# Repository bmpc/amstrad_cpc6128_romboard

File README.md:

# Amstrad CPC 6128 ROM Board

A ROM Board for the Amstrad CPC 6128 capable of loading two expansion ROMs simultaneously from an SD card.

Nowadays, there are plenty of [ROMS available for the Amstrad CPC](http://www.cpcwiki.eu/index.php/ROM_List).
This board allows you to load any ROM present on an SD card as an expansion ROM on the Amstrad CPC 6128. You can bank up to two ROMs at the same time since there are many programs and games that require two ROMs loaded concurrently. In order to select which expansion ROMs should be made available for the Amstrad CPC, the ROM Board provides a small OLED display and buttons that allow the user to browse the SD card files and choose the Upper and Lower ROM specifically.

The ROM board connects to the [expansion port](https://www.cpcwiki.eu/index.php/Connector:Expansion_port) of the Amstrad CPC6128. Here is a picture of the assembled board:

<div style="margin-bottom:20px;">
  
</div>

&nbsp;

## User interface

Upon startup, the selected ROMs for the upper and lower positions are loaded to the SRAM. The display shows the loading progress of each ROM. Once the ROMS are loaded, the display shows the ROM names that are currently loaded.

In order to select ROMs from the SD card, five buttons are provided so that the user can:
 - **SELECT** a given ROM for the upper or lower ROM position
 - **CANCEL** the selected action and return to the loaded ROMs initial screen.
 - Move **UP** and **DOWN** the ROM root folder on the SD card
 - **RESET** the Amstrad CPC and the ROM Board

**Browsing ROMs:**

 - From the main screen, click on the UP or DOWN buttons to enter the browsing mode.
 - In browsing mode, navigate using the UP and DOWN buttons to choose a ROM file from the SD card.

**Selecting a ROM:**

 - Once the desired ROM is chosen, press the SELECT button.
 - A new screen will appear, prompting the user to select the ROM bank position: Lower or Upper.
 - Switch between the lower and upper bank by using the UP and DOWN buttons.

**Saving the ROM:**

 - Press the SELECT button to save the ROM file on the selected bank.
 - To complete the process, restart the Amstrad CPC. This can be done by turning off and on the computer or using the RESET button on the ROM Board.

**Canceling ROM Selection:**

 - If you wish to cancel the ROM selection, press the CANCEL button.
 - You will be returned to the main screen.

## Demonstration video

## The circuit

The circuit can be divided into two parts:
 1. ROM loading, browsing and selection
 2. ROM expansion interface with the Amstrad CPC

The common part between them is the address bugs, the data bus and the SRAM that holds the loaded ROMs.

Ensuring that only one device assumes control of the bus at all times is a crucial aspect to consider. Because we are using the same address and data bus of the Amstrad CPC, when the Amstrad CPC is accessing the bus, the ROM Board shift registers must be tri-stated. Likewise, whenever the ROM Board is accessing the bus in order to load the ROMs, the Amstrad CPC must release control of the bus. This is accomplished by requesting control of the bus through the BUSREQ line being pulled low.

### ROM loading, browsing and selection

The ROM board is based on a atmega328p microcontroller, the same microcontroller that you can find on development boards such as the Arduino Uno. The atmega328p is responsible for loading the selected ROMs (upper and lower) from the SD card into a 32K SRAM (**AS6C62256A**) when the Amstrad CPC boots up.

The loading duration for both ROMs is approximately 5 seconds. Therefore, we need a way to hold the CPC6128 until the ROMs finish loading. This can be achieved using the **BUSREQ** and **BUSACK** lines on the Z80. When the Amstrad CPC starts up, the ROM Board will immediately pull the **BUSREQ** LOW with a pull low resistor. Once the **BUSACK** line is LOW, the Z80 is signaling that control of the address bus, data bus and output signals has been released, and our ROM Board can take control and it starts loading the ROMs. When the atmega328p finishes loading the ROMS, it will pull the **BUSREQ** HIGH and the Z80 resumes processing.

In order to copy the ROM data from the SD card into the SRAM memory, three 8-bit shift registers are used as there aren't enough GPIO pins on the atmega328p for the 15 address lines, 8 data lines and multiple other control signals needed for the ROM board.

Once the ROMs are loaded and the Amstrad CPC has completed the boot process, the user can interact with the ROM Board in order to configure additional ROMs by browsing the SD card and selecting the Upper and Lower ROM. The selected ROMs will be saved within the atmega328p internal EEPROM. In order to load the newly selected ROMs, the Amstrad CPC and the ROM Board must be restarted.

### ROM expansion interface with the Amstrad CPC

Whenever the CPC wants to communicate with the Upper ROM, it will first write a byte with the selected Upper ROM bank number into port **$DF00**. There can be up to 252 expansion ROMS mapped over the top 16K of memory, starting at #C000. After this, the **ROMEN** signal will go LOW, and the CPC will start addressing the Upper ROM.

We must guarantee that there is a unique Upper ROM enabled at any given time. Therefore, whenever an expansion ROM is active, the internal CPC Upper ROM must be disabled. This is done by bringing the **ROMDIS** line LOW, a signal conveniently provided by the CPC for this purpose. After this, any memory requests to the ROM’s address space will be handled solely by the selected expansion ROM.

The CPC does not store the selected ROM Bank number anywhere. Peripheral devices are responsible for latching the selected ROM bank whenever the bank number is written to port **$DF00**.

Our ROM Board supports up to two ROMs mapped for the Amstrad CPC Upper ROM bank. These ROMs are located at positions **#14** and **#15** (that we call Upper and Lower ROMS on the ROM Board).

Whenever the Amstrad CPC tries to select a given ROM through the IO port, if the ROM being selected is provided by the ROM Board (#14 or #15) then a latch is used to store this information. Another latch is used to store which of the ROMs was selected: #14 or #15. A Dual D-Type flipflop (SN74HC74N) was used for these latches.

The Tristate buffer (SN74HC126N) is used to tie the A14 line to the selected upper or lower ROM stored in the previous latch. The A14 line must be tri-stated from the Amstrad CPC bus whenever the ROMS are being loaded.

You can find more detail information regarding the build of this ROM Board in the following post:
[https://bmpc.github.io/amstrad-cpc-rom-board](https://bmpc.github.io/amstrad-cpc-rom-board/).

### Schematic

<div style="text-align:center">
  
</div>

### BOM

 - Atmega328             x1
 - 74HC595N              x3 (shift registers)
 - 74HC74N               x1 (D FlipFlop)
 - 74HC21N               x2 (Dual 4-input AND gate)
 - 74HC126N              x1 (3-state bus buffer)
 - 74HC02N               x1 (Quad 2-input NOR gate)
 - AS6C62256A            x1 (32k sram)
 - 10kΩ  resistor        x1
 - 1.8Ω  resistor        x1
 - 1Ω    resistor        x5
 - 220Ω  resistor        x1
 - 1N4148                x1 (Standard Diode 300mA 75V)
 - 22pF 50V capacitor    x2
 - Push Buttons          x5
 - Cristal 16Mhz         x1
 - MicroSD card breakout x1 (adafruit)
 - 0.96inch OLED         x1 (0.96inch OLED 128X64 w/ SPI/I2C interfaces and vertical pinheader 4pin - White)
 - 02x25 socket          x1 (expansion port)

## References

 - [Building an Amstrad CPC expansion ROM in a breadboard](https://bmpc.github.io/bulding-an-amstrad-cpc-expansion-rom)
 - [Amstrad CPC 6128 ROM Board](https://bmpc.github.io/amstrad-cpc-rom-board)
 - https://www.cpcwiki.eu/index.php/ACU_Romboard_(DIY)
 - https://www.cpcwiki.eu/imgs/3/32/Amstrad_rom_expander.pdf

## *Disclaimer*
*I'm a software engineer with no background in electronics. Please don't consider what you read here to be best practice. Use at your own risk.*

*Nevertheless, feedback is always welcome.*

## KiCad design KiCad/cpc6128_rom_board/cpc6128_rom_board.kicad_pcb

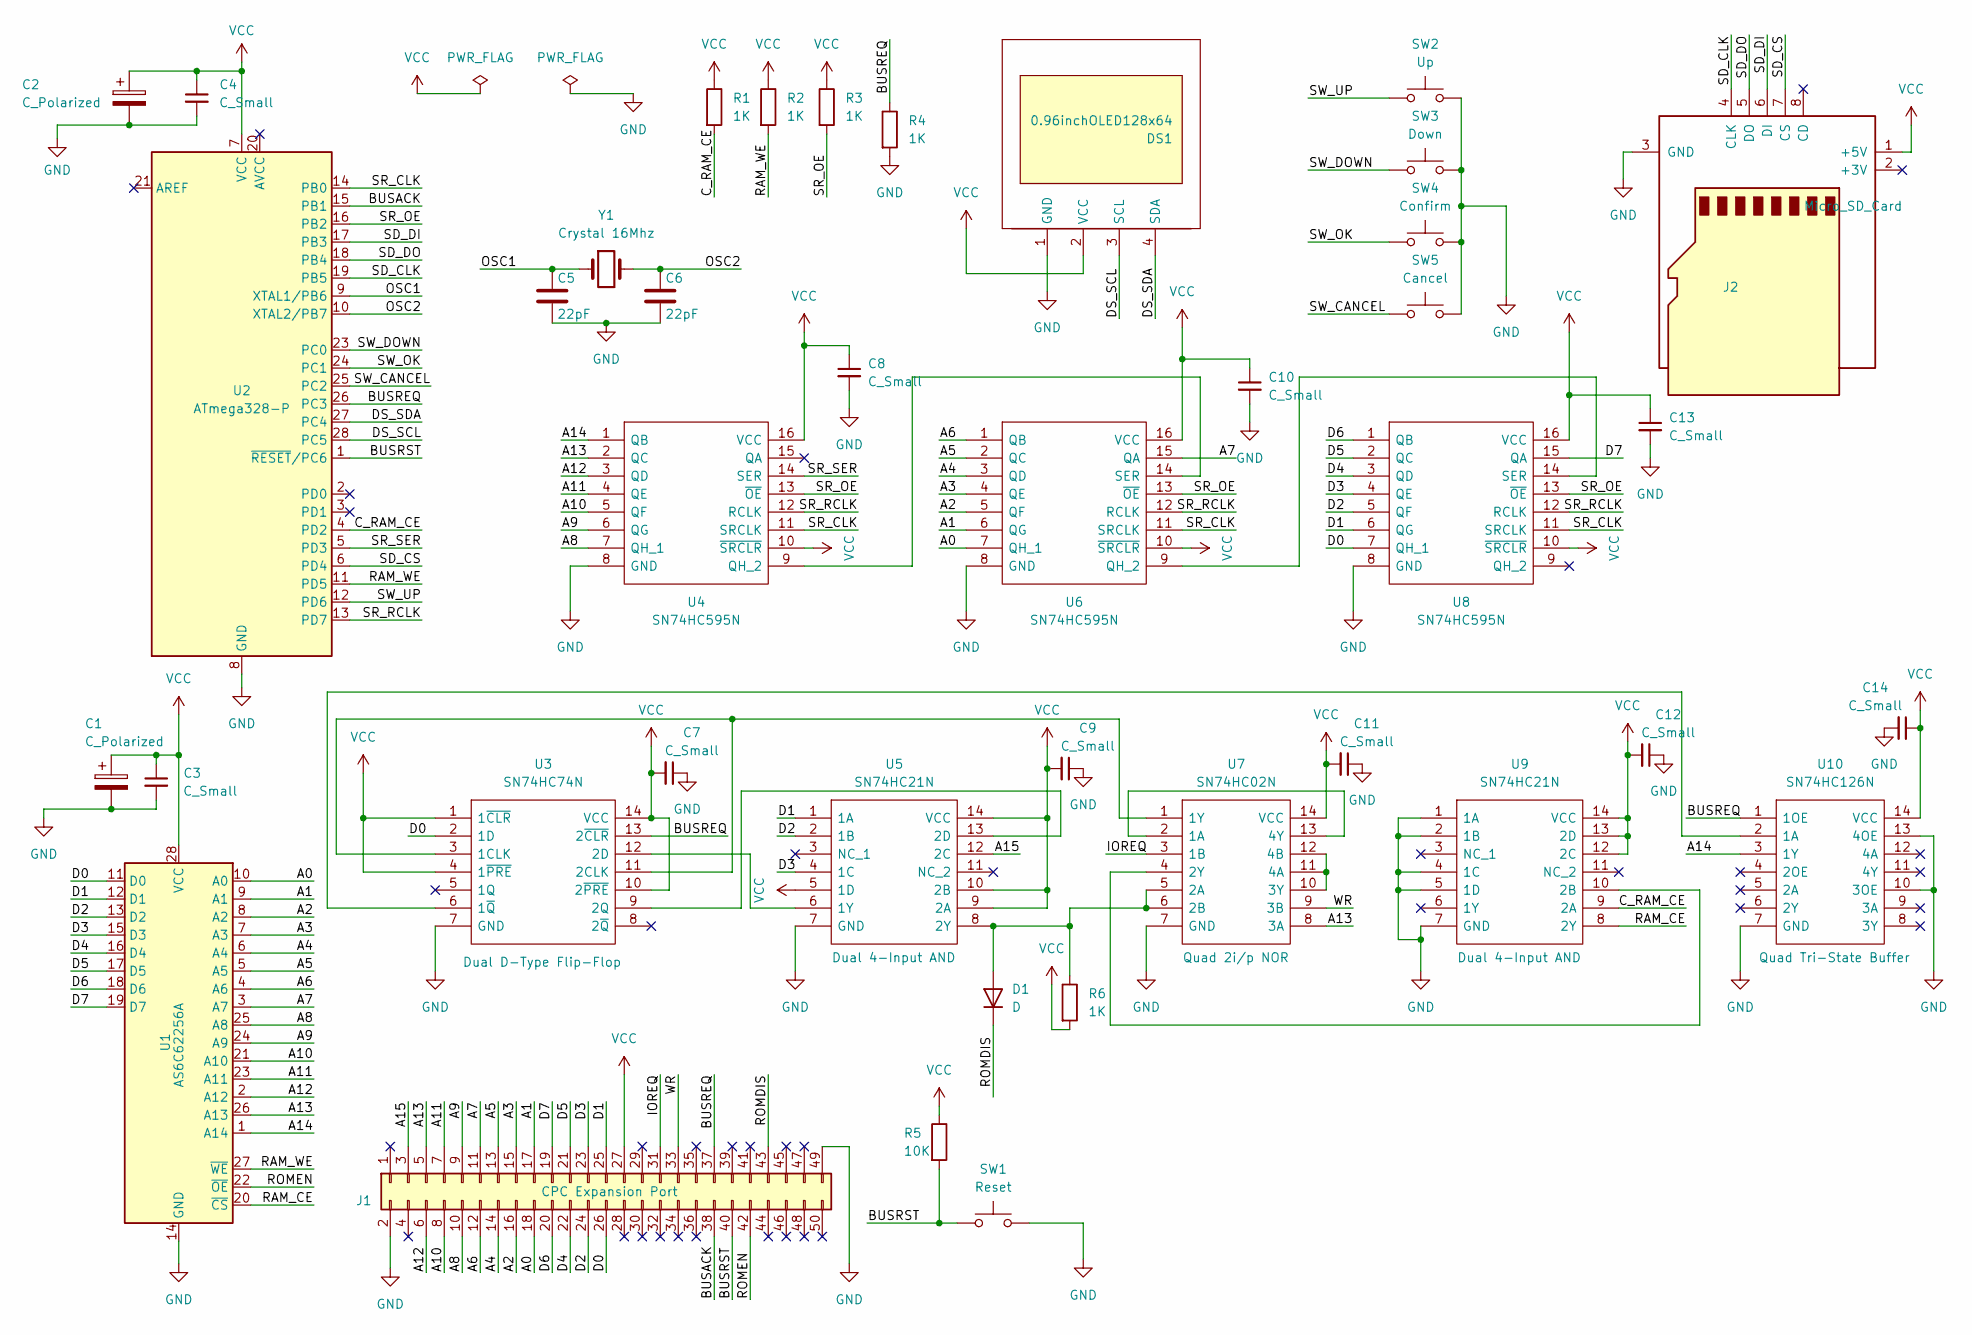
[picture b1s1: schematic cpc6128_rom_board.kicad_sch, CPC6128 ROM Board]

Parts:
C1, C2: C_Polarized; CP_Radial_D4.0mm_P2.00mm
C3, C4, C7, C8, C9, C10, C11, C12, C13, C14: C_Small; C_Disc_D3.0mm_W1.6mm_P2.50mm
C5, C6: 22pF; C_Disc_D3.0mm_W1.6mm_P2.50mm
D1: D; D_A-405_P7.62mm_Horizontal
DS1: 0.96inchOLED128x64
J1: CPC Expansion Port; IDC-Header_2x25_P2.54mm_Vertical
J2: Micro_SD_Card; Micro_SD_Card_breakout_board
R1, R2, R3, R4, R6: 1K; R_Axial_DIN0207_L6.3mm_D2.5mm_P7.62mm_Horizontal
R5: 10K; R_Axial_DIN0207_L6.3mm_D2.5mm_P7.62mm_Horizontal
SW1: Reset; SW_PUSH-12mm_Wuerth-430476085716
SW2: Up; SW_PUSH-12mm_Wuerth-430476085716
SW3: Down; SW_PUSH-12mm_Wuerth-430476085716
SW4: Confirm; SW_PUSH-12mm_Wuerth-430476085716
SW5: Cancel; SW_PUSH-12mm_Wuerth-430476085716
U1: AS6C62256A; DIP-28_W15.24mm
U2: ATmega328-P; DIP-28_W7.62mm
U3: SN74HC74N; DIP-14_W7.62mm_Socket; Manufacturer_Part_Number SN74HC74N; Mouser Part Number 595-SN74HC74N
U4, U6, U8: SN74HC595N; DIP-16_W7.62mm_Socket; Manufacturer_Part_Number SN74HC595N; Mouser Part Number 595-SN74HC595N
U5, U9: SN74HC21N; DIP-14_W7.62mm_Socket; Manufacturer_Part_Number SN74HC21N; Mouser Part Number 595-SN74HC21N
U7: SN74HC02N; DIP-14_W7.62mm_Socket; Manufacturer_Part_Number SN74HC02N; Mouser Part Number 595-SN74HC02N
U10: SN74HC126N; DIP-14_W7.62mm_Socket; Manufacturer_Part_Number SN74HC126N; Mouser Part Number 595-SN74HC126N
Y1: Crystal 16Mhz; Crystal_HC18-U_Vertical

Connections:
/A0: J1.18, U1.10 (A0), U6.7 (QH_1)
/A1: J1.17, U1.9 (A1), U6.6 (QG)
/A2: J1.16, U1.8 (A2), U6.5 (QF)
/A3: J1.15, U1.7 (A3), U6.4 (QE)
/A4: J1.14, U1.6 (A4), U6.3 (QD)
/A5: J1.13, U1.5 (A5), U6.2 (QC)
/A6: J1.12, U1.4 (A6), U6.1 (QB)
/A7: J1.11, U1.3 (A7), U6.15 (QA)
/A8: J1.10, U1.25 (A8), U4.7 (QH_1)
/A9: J1.9, U1.24 (A9), U4.6 (QG)
/A10: J1.8, U1.21 (A10), U4.5 (QF)
/A11: J1.7, U1.23 (A11), U4.4 (QE)
/A12: J1.6, U1.2 (A12), U4.3 (QD)
/A13: J1.5, U1.26 (A13), U4.2 (QC), U7.8 (3A)
/A14: U1.1 (A14), U4.1 (QB), U10.3 (1Y)
/A15: J1.3, U5.12 (2C)
/BUSACK: J1.38, U2.15 (PB1)
/BUSREQ: J1.37, R4.1, U2.26 (PC3), U3.13 (2~CLR), U10.1 (1OE)
/BUSRST: J1.40, R5.2, SW1.1, U2.1 (~RESET/PC6)
/C_RAM_CE: R1.2, U2.4 (PD2), U9.9 (2A)
/D0: J1.26, U1.11 (D0), U3.2 (1D), U8.7 (QH_1)
/D1: J1.25, U1.12 (D1), U5.1 (1A), U8.6 (QG)
/D2: J1.24, U1.13 (D2), U5.2 (1B), U8.5 (QF)
/D3: J1.23, U1.15 (D3), U5.4 (1C), U8.4 (QE)
/D4: J1.22, U1.16 (D4), U8.3 (QD)
/D5: J1.21, U1.17 (D5), U8.2 (QC)
/D6: J1.20, U1.18 (D6), U8.1 (QB)
/D7: J1.19, U1.19 (D7), U8.15 (QA)
/DS_SCL: DS1.3 (SCL), U2.28 (PC5)
/DS_SDA: DS1.4 (SDA), U2.27 (PC4)
/IOREQ: J1.31, U7.3 (1B)
/OSC1: C5.1, U2.9 (XTAL1/PB6), Y1.1
/OSC2: C6.1, U2.10 (XTAL2/PB7), Y1.2
/RAM_CE: U1.20 (~CS), U9.8 (2Y)
/RAM_WE: R2.2, U1.27 (~WE), U2.11 (PD5)
/ROMDIS: D1.1 (K), J1.43
/ROMEN: J1.42, U1.22 (~OE)
/SD_CLK: J2.4 (CLK), U2.19 (PB5)
/SD_CS: J2.7 (CS), U2.6 (PD4)
/SD_DI: J2.6 (DI), U2.17 (PB3)
/SD_DO: J2.5 (DO), U2.18 (PB4)
/SR_CLK: U2.14 (PB0), U4.11 (SRCLK), U6.11 (SRCLK), U8.11 (SRCLK)
/SR_OE: R3.2, U2.16 (PB2), U4.13 (~OE), U6.13 (~OE), U8.13 (~OE)
/SR_RCLK: U2.13 (PD7), U4.12 (RCLK), U6.12 (RCLK), U8.12 (RCLK)
/SR_SER: U2.5 (PD3), U4.14 (SER)
/SW_CANCEL: SW5.1, U2.25 (PC2)
/SW_DOWN: SW3.1, U2.23 (PC0)
/SW_OK: SW4.1, U2.24 (PC1)
/SW_UP: SW2.1, U2.12 (PD6)
/WR: J1.33, U7.9 (3B)
GND: C1.2, C2.2, C3.2, C4.2, C5.2, C6.2, C7.1, C8.2, C9.1, C10.2, C11.1, C12.1, C13.2, C14.2, DS1.1 (GND), J1.2, J1.49, J2.3 (GND), R4.2, SW1.2, SW2.2, SW3.2, SW4.2, SW5.2, U1.14 (GND), U2.8 (GND), U2.22 (GND), U3.7 (GND), U4.8 (GND), U5.7 (GND), U6.8 (GND), U7.7 (GND), U8.8 (GND), U9.1 (1A), U9.2 (1B), U9.4 (1C), U9.5 (1D), U9.7 (GND), U10.7 (GND), U10.10 (3OE), U10.13 (4OE)
unnamed: D1.2 (A), R6.1, U5.8 (2Y), U7.5 (2A), U7.6 (2B)
unnamed: U3.9 (2Q), U5.13 (2D)
unnamed: U3.3 (1CLK), U3.11 (2CLK), U7.1 (1Y)
unnamed: U3.12 (2D), U5.6 (1Y)
unnamed: U4.9 (QH_2), U6.14 (SER)
unnamed: U6.9 (QH_2), U8.14 (SER)
unnamed: U7.4 (2Y), U9.10 (2B)
unnamed: U7.10 (3Y), U7.11 (4A), U7.12 (4B)
unnamed: U7.2 (1A), U7.13 (4Y)
unnamed: U3.6 (1~Q), U10.2 (1A)
VCC: C1.1, C2.1, C3.1, C4.1, C7.2, C8.1, C9.2, C10.1, C11.2, C12.2, C13.1, C14.1, DS1.2 (VCC), J1.27, J2.1 (+5V), R1.1, R2.1, R3.1, R5.1, R6.2, U1.28 (VCC), U2.7 (VCC), U3.1 (1~CLR), U3.4 (1~PRE), U3.10 (2~PRE), U3.14 (VCC), U4.10 (~SRCLR), U4.16 (VCC), U5.5 (1D), U5.9 (2A), U5.10 (2B), U5.14 (VCC), U6.10 (~SRCLR), U6.16 (VCC), U7.14 (VCC), U8.10 (~SRCLR), U8.16 (VCC), U9.12 (2C), U9.13 (2D), U9.14 (VCC), U10.14 (VCC)

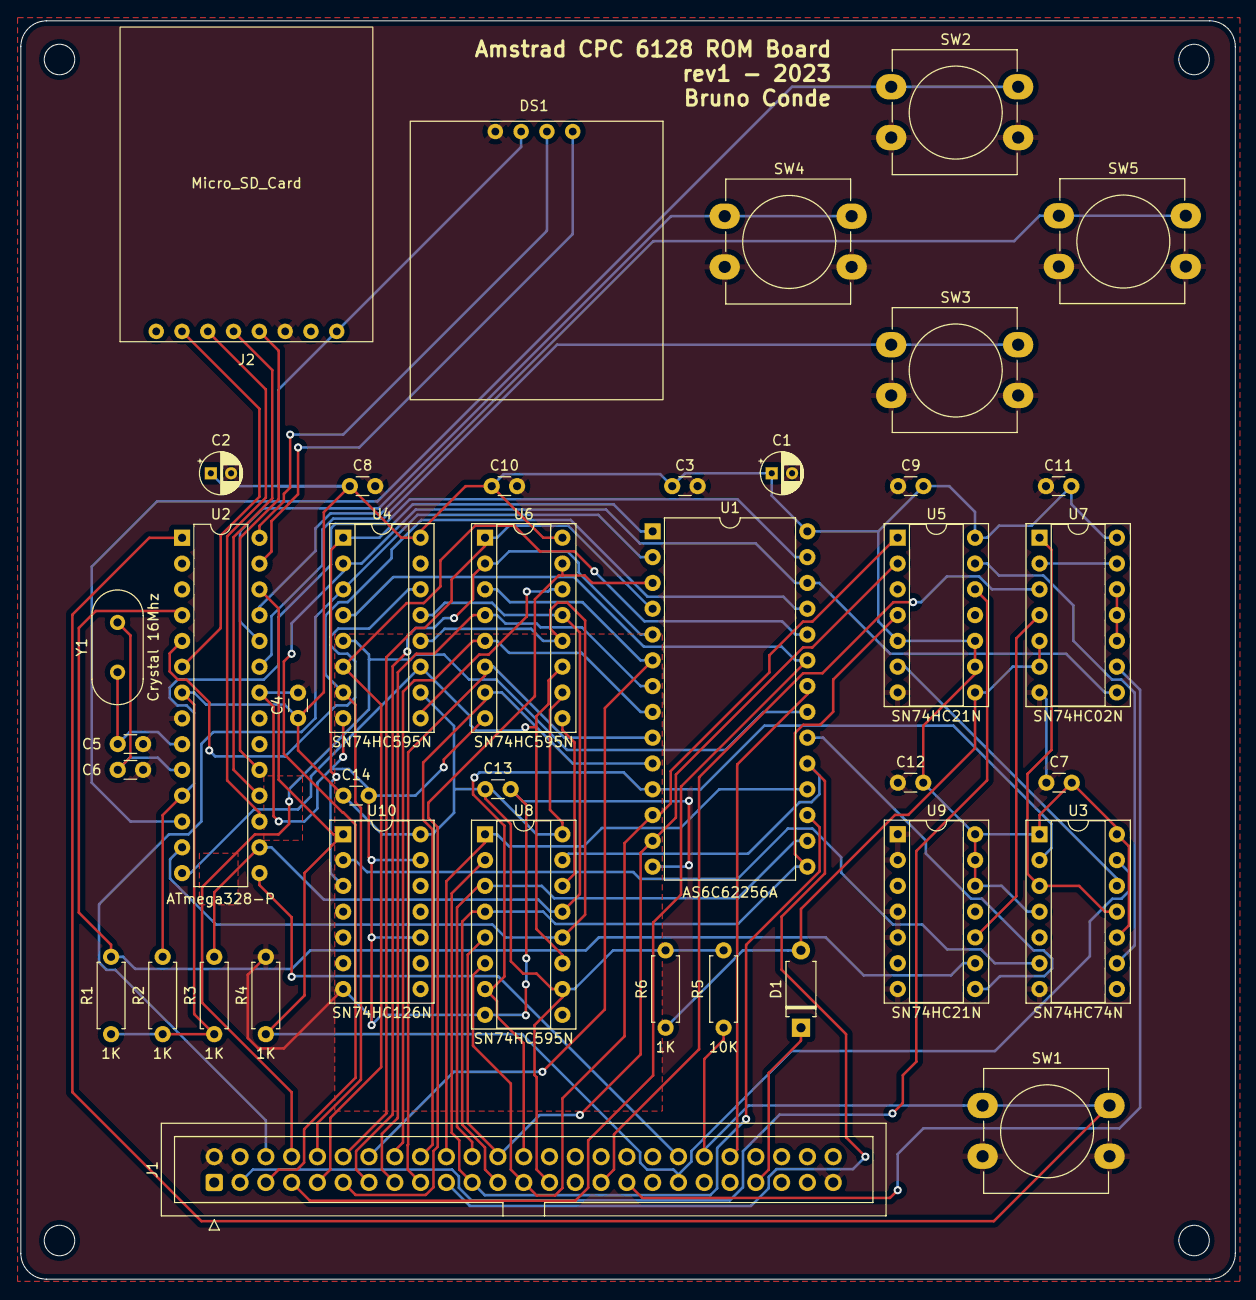
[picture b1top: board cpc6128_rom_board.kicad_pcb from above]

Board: 2 copper layers, 119.6 x 123.9 mm, 44 parts (0 on the bottom side), 62 nets.

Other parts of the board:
Hole1, Hole2, Hole3, Hole4: MountingHole_3mm

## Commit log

2021-10-04 Ignoring some project folders
2021-11-01 Initial sram version
2022-01-16 Working version using SRAM
2022-04-01 Adding a UP button so that we can navigate to the previous file.
2022-05-02 Hack to move to the previous file handle
2022-05-03 Working on a solution to navigate backwards within the directory file entries
2022-05-10 Added a fast way of iterating through the list of files in the root folder of an SD card, forward and backward
2023-06-25 Moved some components from namespaces to classes; Adding the Kicad project for the ROM Board; Added the README and some pictures of the board
